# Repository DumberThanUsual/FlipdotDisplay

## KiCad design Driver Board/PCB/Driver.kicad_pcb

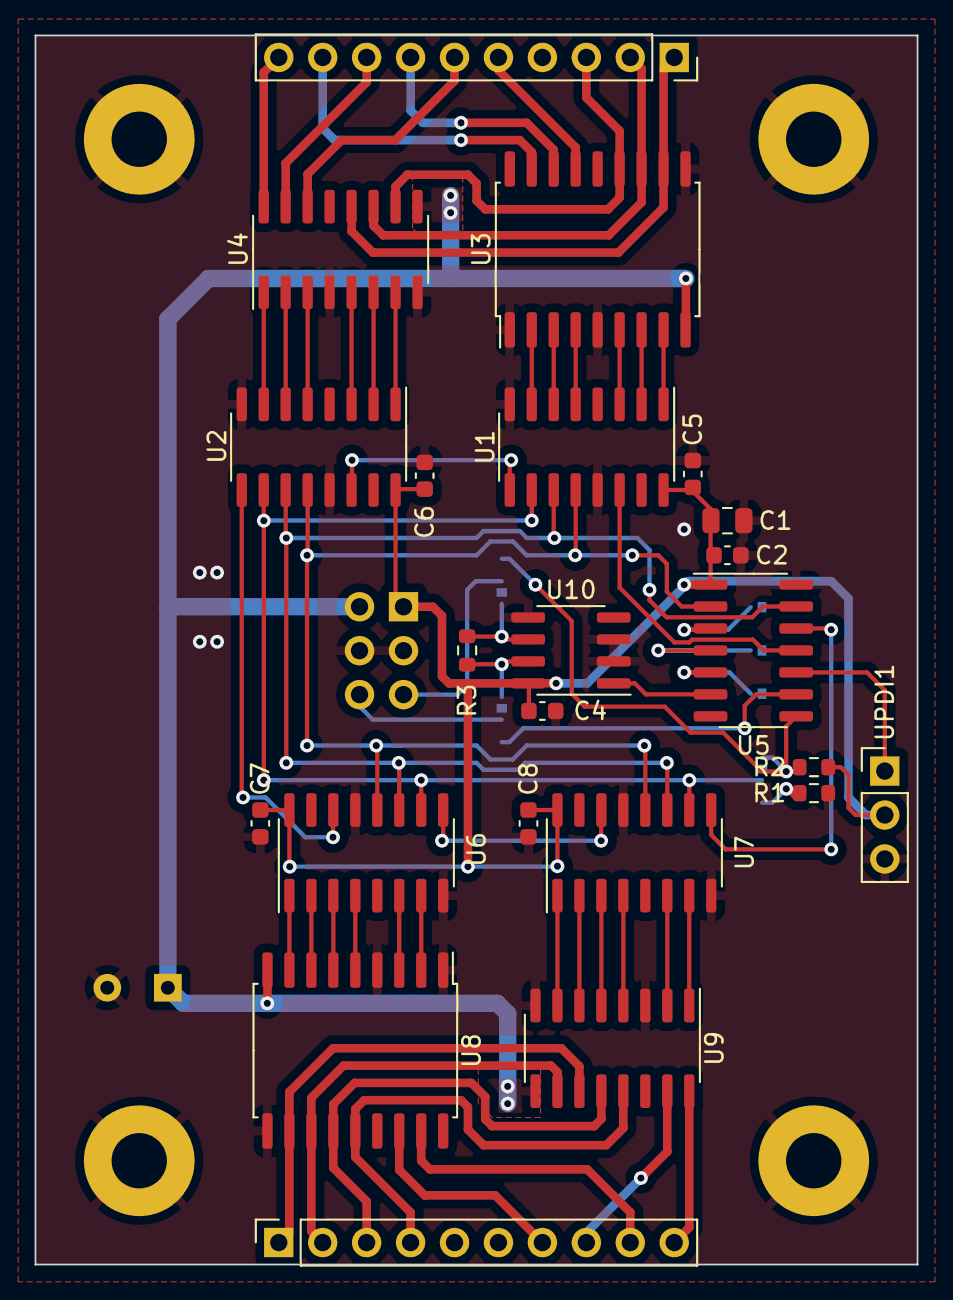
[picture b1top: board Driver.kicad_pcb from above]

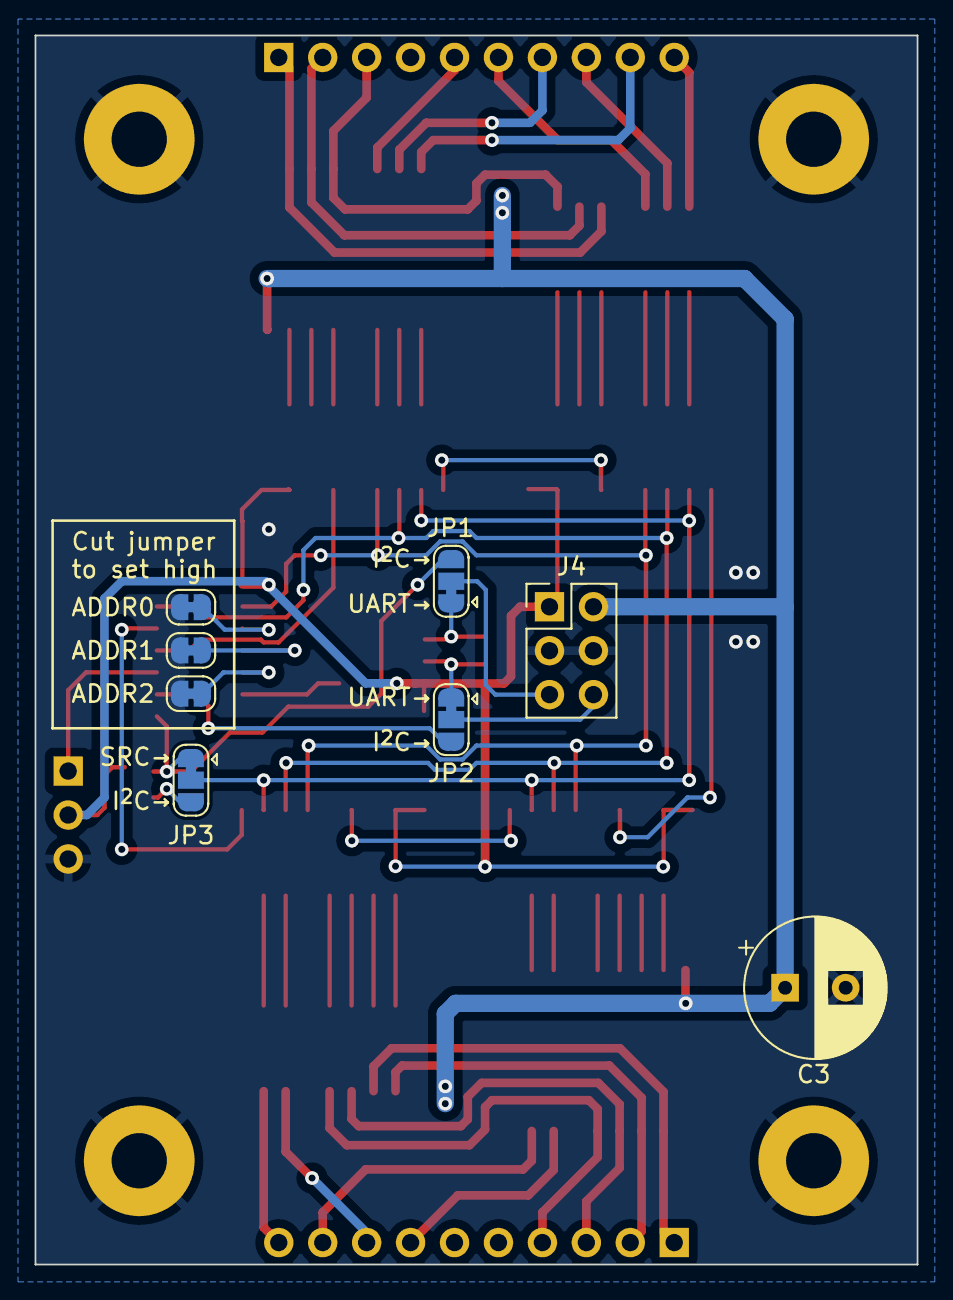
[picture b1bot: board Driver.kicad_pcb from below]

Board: 2 copper layers, 51.0 x 71.0 mm, 35 parts (8 on the bottom side), 64 nets.

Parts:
ADDR0: ADDR0; SolderJumper-2_P1.3mm_Bridged_RoundedPad1.0x1.5mm
ADDR1: ADDR1; SolderJumper-2_P1.3mm_Bridged_RoundedPad1.0x1.5mm
ADDR2: ADDR2; SolderJumper-2_P1.3mm_Bridged_RoundedPad1.0x1.5mm
C1: 22u; C_0805_2012Metric
C2, C4, C5, C6, C7, C8: 100n; C_0603_1608Metric
C3: 470u; CP_Radial_D8.0mm_P3.50mm
H1, H2, H3, H4: MountingHole; MountingHole_3.2mm_M3_Pad
J2, J3: Conn_01x10_Pin; PinSocket_1x10_P2.54mm_Vertical
J4: BHR-06-VUA; PinHeader_2x03_P2.54mm_Vertical
JP1, JP2, JP3: SolderJumper_3_Bridged12; SolderJumper-3_P1.3mm_Bridged12_RoundedPad1.0x1.5mm
R1, R2: 100k; R_0603_1608Metric
R3: R_{term}; R_0603_1608Metric
U1, U2, U6, U7: 74HC595; SOIC-16_3.9x9.9mm_P1.27mm
U3, U8: TBD62783A; SOIC-18W_7.5x11.6mm_P1.27mm
U4, U9: ULN2003A; SOIC-16_3.9x9.9mm_P1.27mm
U5: ATtiny424-SS; SOIC-14_3.9x8.7mm_P1.27mm
U10: THVD1420D; SOIC-8_3.9x4.9mm_P1.27mm
UPDI1: Conn_01x03_Pin; PinHeader_1x03_P2.54mm_Vertical

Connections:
/C1H: J3.9, U3.17 (O2)
/C1L: J3.10, U4.16 (O1)
/C2H: J3.7, U3.16 (O3)
/C2L: J3.8, U4.15 (O2)
/C3H: J3.5, U3.15 (O4)
/C3L: J3.6, U4.14 (O3)
/C4H: J2.7, U8.16 (O3)
/C4L: J2.8, U9.15 (O2)
/C5H: J2.9, U8.17 (O2)
/C5L: J2.10, U9.16 (O1)
/D1: U1.1 (QB), U3.8 (I8)
/D2: U1.2 (QC), U3.7 (I7)
/D3: U1.3 (QD), U3.6 (I6)
/D5: U1.5 (QF), U3.4 (I4)
/D6: U1.6 (QG), U3.3 (I3)
/D7: U1.7 (QH), U3.2 (I2)
/D9: U2.1 (QB), U4.7 (I7)
/D10: U2.2 (QC), U4.6 (I6)
/D11: U2.3 (QD), U4.5 (I5)
/D13: U2.5 (QF), U4.3 (I3)
/D14: U2.6 (QG), U4.2 (I2)
/D15: U2.7 (QH), U4.1 (I1)
/D17: U6.1 (QB), U8.8 (I8)
/D18: U6.2 (QC), U8.7 (I7)
/D19: U6.3 (QD), U8.6 (I6)
/D20: U6.4 (QE), U8.5 (I5)
/D22: U6.6 (QG), U8.3 (I3)
/D23: U6.7 (QH), U8.2 (I2)
/D25: U7.1 (QB), U9.7 (I7)
/D26: U7.2 (QC), U9.6 (I6)
/D27: U7.3 (QD), U9.5 (I5)
/D28: U7.4 (QE), U9.4 (I4)
/D30: U7.6 (QG), U9.2 (I2)
/D31: U7.7 (QH), U9.1 (I1)
/I^{2}C_SCL: JP2.3 (B), U5.9 (PB0)
/I^{2}C_SDA: JP1.3 (B), JP3.1 (A), R2.2, U5.8 (PB1)
/RCLK: U1.12 (RCLK), U2.12 (RCLK), U5.2 (PA4), U6.12 (RCLK), U7.12 (RCLK)
/RS485_A: JP1.1 (A), R3.1, U10.6 (A)
/RS485_B: JP2.1 (A), R3.2, U10.7 (B)
/SA: J2.1, U8.11 (O8), U9.11 (O6)
/SB: J2.2, U8.12 (O7), U9.10 (O7)
/SC: J2.3, U8.13 (O6), U9.12 (O5)
/SD: J2.4, U8.14 (O5), U9.13 (O4)
/SE: J3.3, U3.13 (O6), U4.10 (O7)
/SER': U2.9 (QH'), U6.14 (SER)
/SEROUT: U5.12 (PA2), U7.9 (QH')
/SF: J3.2, U3.12 (O7), U4.11 (O6)
/SG: J3.1, U3.11 (O8), U4.12 (O5)
/SRCLK: U1.11 (SRCLK), U2.11 (SRCLK), U5.13 (PA3), U6.11 (SRCLK), U7.11 (SRCLK)
/SRIN: U1.14 (SER), U5.11 (PA1)
/UART_RXD: U5.6 (PB3), U10.1 (RO)
/~RST/UPDI: U5.10 (~RESET/PA0), UPDI1.1
/~SRCLR: JP3.2 (C), U1.10 (~SRCLR), U2.10 (~SRCLR), U6.10 (~SRCLR), U7.10 (~SRCLR)
GND: ADDR0.2 (B), ADDR1.2 (B), ADDR2.2 (B), C1.2, C2.2, C3.2, C4.2, C5.2, C6.2, C7.2, C8.2, H1.1, H2.1, H3.1, H4.1, J4.3, J4.4, R1.1, U1.8 (GND), U1.13 (~OE), U2.8 (GND), U2.13 (~OE), U3.1 (I1), U3.5 (I5), U3.10 (GND), U4.4 (I4), U4.8 (GND), U5.14 (GND), U6.8 (GND), U6.13 (~OE), U7.8 (GND), U7.13 (~OE), U8.1 (I1), U8.4 (I4), U8.10 (GND), U9.3 (I3), U9.8 (GND), U10.2 (~RE), U10.3 (DE), U10.5 (GND), UPDI1.3
unnamed: ADDR0.1 (A), U5.3 (PA5)
unnamed: ADDR1.1 (A), U5.4 (PA6)
unnamed: ADDR2.1 (A), U5.5 (PA7)
unnamed: J4.5, JP1.2 (C)
unnamed: J4.6, JP2.2 (C)
unnamed: JP3.3 (B), R1.2
unnamed: U1.9 (QH'), U2.14 (SER)
unnamed: U6.9 (QH'), U7.14 (SER)
VCC: C1.1, C2.1, C4.1, C5.1, C6.1, C7.1, C8.1, J4.1, R2.1, U1.16 (VCC), U2.16 (VCC), U5.1 (VCC), U6.16 (VCC), U7.16 (VCC), U10.8 (VCC), UPDI1.2
Vdrive: C3.1, J4.2, U3.9 (VCC), U4.9 (COM), U8.9 (VCC), U9.9 (COM)

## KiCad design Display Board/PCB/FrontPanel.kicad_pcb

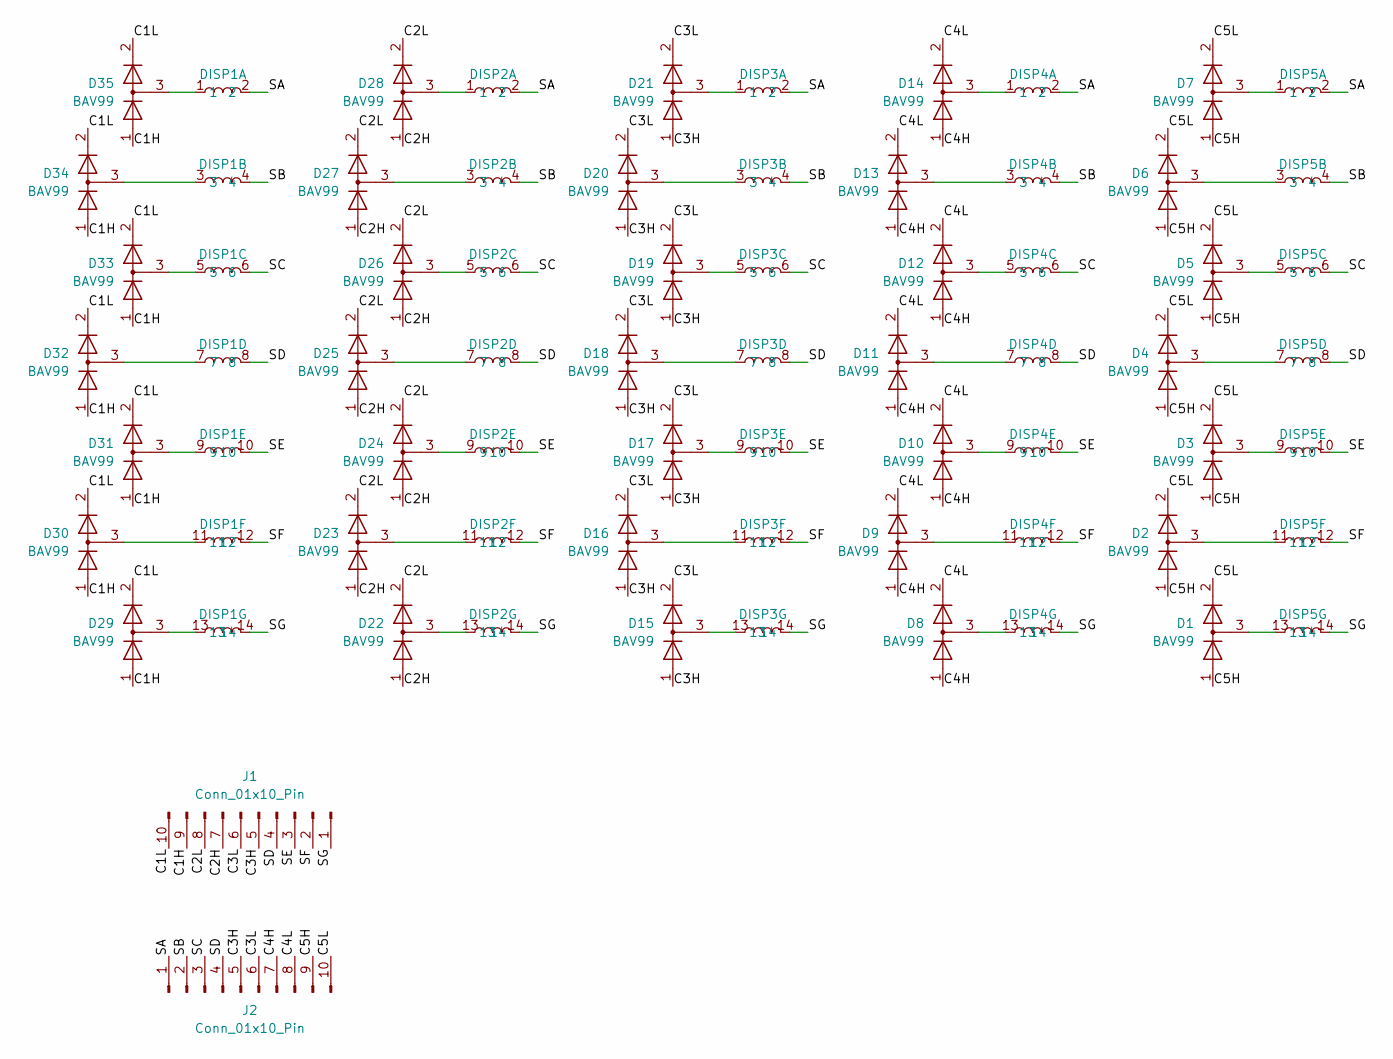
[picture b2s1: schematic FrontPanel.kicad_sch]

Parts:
D1, D2, D3, D4, D5, D6, D7, D8, D9, D10, D11, D12, D13, D14, D15, D16, D17, D18, D19, D20, D21, D22, D23, D24, D25, D26, D27, D28, D29, D30, D31, D32, D33, D34, D35: BAV99; SOT-23
DISP1, DISP2, DISP3, DISP4, DISP5: 1x7
J1, J2: Conn_01x10_Pin; PinHeader_1x10_P2.54mm_Vertical

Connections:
/C1H: D29.1 (K), D30.1 (K), D31.1 (K), D32.1 (K), D33.1 (K), D34.1 (K), D35.1 (K), J1.9
/C1L: D29.2 (A), D30.2 (A), D31.2 (A), D32.2 (A), D33.2 (A), D34.2 (A), D35.2 (A), J1.10
/C2H: D22.1 (K), D23.1 (K), D24.1 (K), D25.1 (K), D26.1 (K), D27.1 (K), D28.1 (K), J1.7
/C2L: D22.2 (A), D23.2 (A), D24.2 (A), D25.2 (A), D26.2 (A), D27.2 (A), D28.2 (A), J1.8
/C3H: D15.1 (K), D16.1 (K), D17.1 (K), D18.1 (K), D19.1 (K), D20.1 (K), D21.1 (K), J1.5, J2.5
/C3L: D15.2 (A), D16.2 (A), D17.2 (A), D18.2 (A), D19.2 (A), D20.2 (A), D21.2 (A), J1.6, J2.6
/C4H: D8.1 (K), D9.1 (K), D10.1 (K), D11.1 (K), D12.1 (K), D13.1 (K), D14.1 (K), J2.7
/C4L: D8.2 (A), D9.2 (A), D10.2 (A), D11.2 (A), D12.2 (A), D13.2 (A), D14.2 (A), J2.8
/C5H: D1.1 (K), D2.1 (K), D3.1 (K), D4.1 (K), D5.1 (K), D6.1 (K), D7.1 (K), J2.9
/C5L: D1.2 (A), D2.2 (A), D3.2 (A), D4.2 (A), D5.2 (A), D6.2 (A), D7.2 (A), J2.10
/SA: DISP1.2, DISP2.2, DISP3.2, DISP4.2, DISP5.2, J2.1
/SB: DISP1.4, DISP2.4, DISP3.4, DISP4.4, DISP5.4, J2.2
/SC: DISP1.6, DISP2.6, DISP3.6, DISP4.6, DISP5.6, J2.3
/SD: DISP1.8, DISP2.8, DISP3.8, DISP4.8, DISP5.8, J1.4, J2.4
/SE: DISP1.10, DISP2.10, DISP3.10, DISP4.10, DISP5.10, J1.3
/SF: DISP1.12, DISP2.12, DISP3.12, DISP4.12, DISP5.12, J1.2
/SG: DISP1.14, DISP2.14, DISP3.14, DISP4.14, DISP5.14, J1.1
unnamed: D1.3 (K), DISP5.13
unnamed: D2.3 (K), DISP5.11
unnamed: D3.3 (K), DISP5.9
unnamed: D4.3 (K), DISP5.7
unnamed: D5.3 (K), DISP5.5
unnamed: D6.3 (K), DISP5.3
unnamed: D7.3 (K), DISP5.1
unnamed: D8.3 (K), DISP4.13
unnamed: D9.3 (K), DISP4.11
unnamed: D10.3 (K), DISP4.9
unnamed: D11.3 (K), DISP4.7
unnamed: D12.3 (K), DISP4.5
unnamed: D13.3 (K), DISP4.3
unnamed: D14.3 (K), DISP4.1
unnamed: D15.3 (K), DISP3.13
unnamed: D16.3 (K), DISP3.11
unnamed: D17.3 (K), DISP3.9
unnamed: D18.3 (K), DISP3.7
unnamed: D19.3 (K), DISP3.5
unnamed: D20.3 (K), DISP3.3
unnamed: D21.3 (K), DISP3.1
unnamed: D22.3 (K), DISP2.13
unnamed: D23.3 (K), DISP2.11
unnamed: D24.3 (K), DISP2.9
unnamed: D25.3 (K), DISP2.7
unnamed: D26.3 (K), DISP2.5
unnamed: D27.3 (K), DISP2.3
unnamed: D28.3 (K), DISP2.1
unnamed: D29.3 (K), DISP1.13
unnamed: D30.3 (K), DISP1.11
unnamed: D31.3 (K), DISP1.9
unnamed: D32.3 (K), DISP1.7
unnamed: D33.3 (K), DISP1.5
unnamed: D34.3 (K), DISP1.3
unnamed: D35.3 (K), DISP1.1

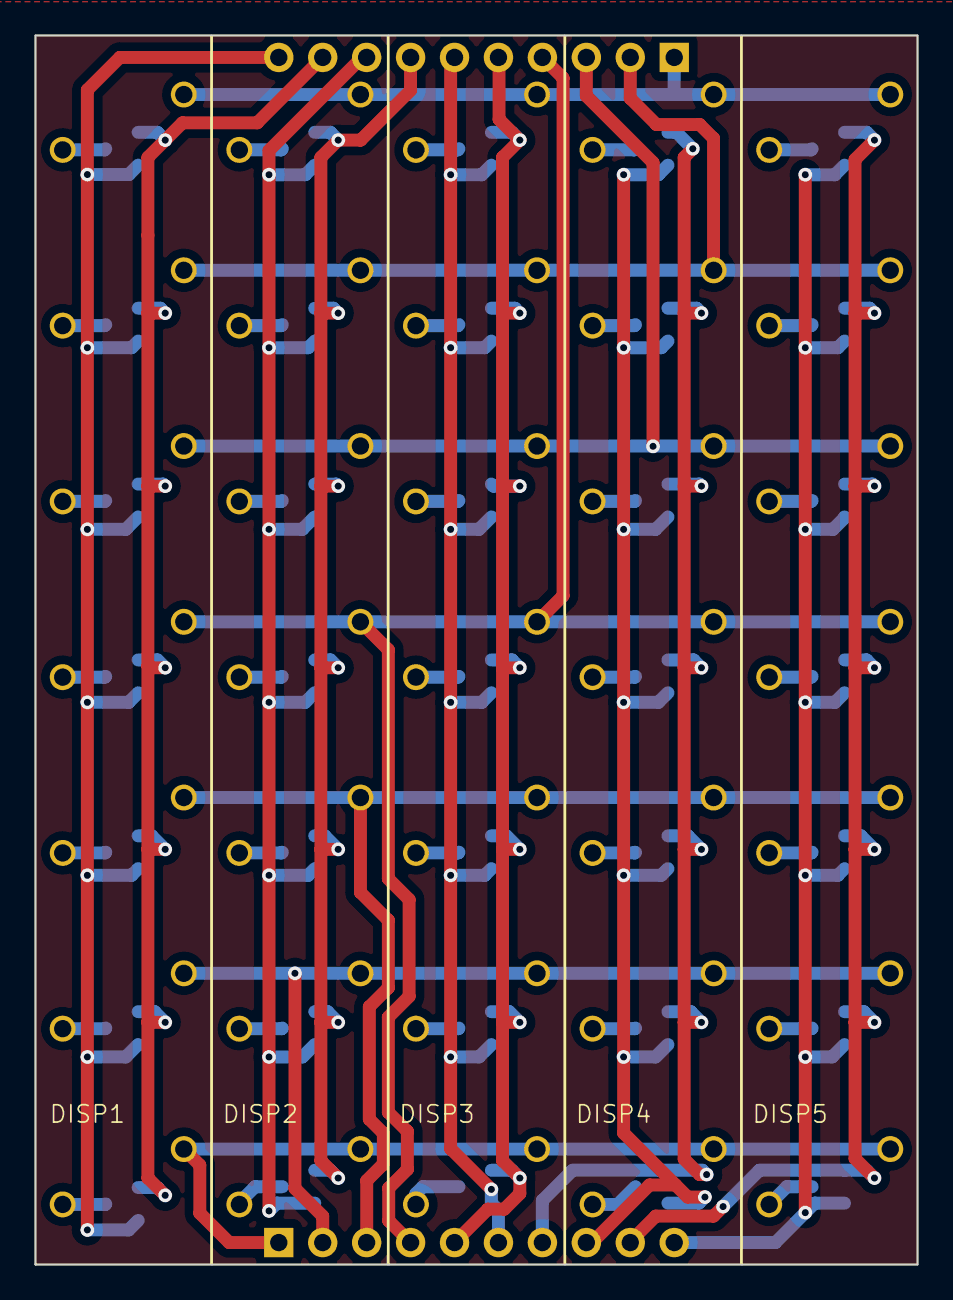
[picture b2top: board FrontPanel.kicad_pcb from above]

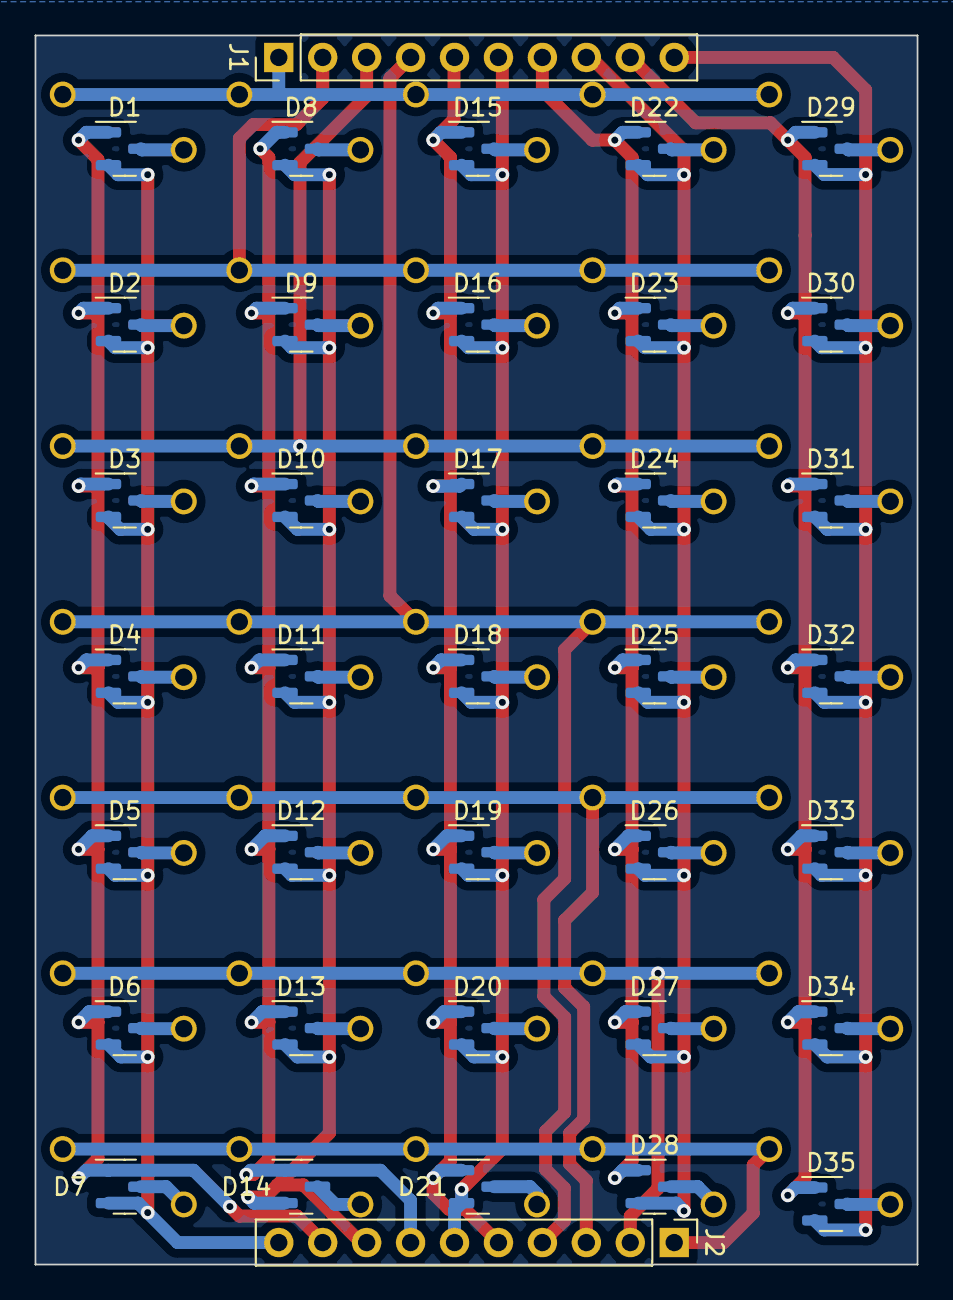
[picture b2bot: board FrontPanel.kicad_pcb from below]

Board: 2 copper layers, 51.0 x 71.0 mm, 42 parts (37 on the bottom side), 52 nets.

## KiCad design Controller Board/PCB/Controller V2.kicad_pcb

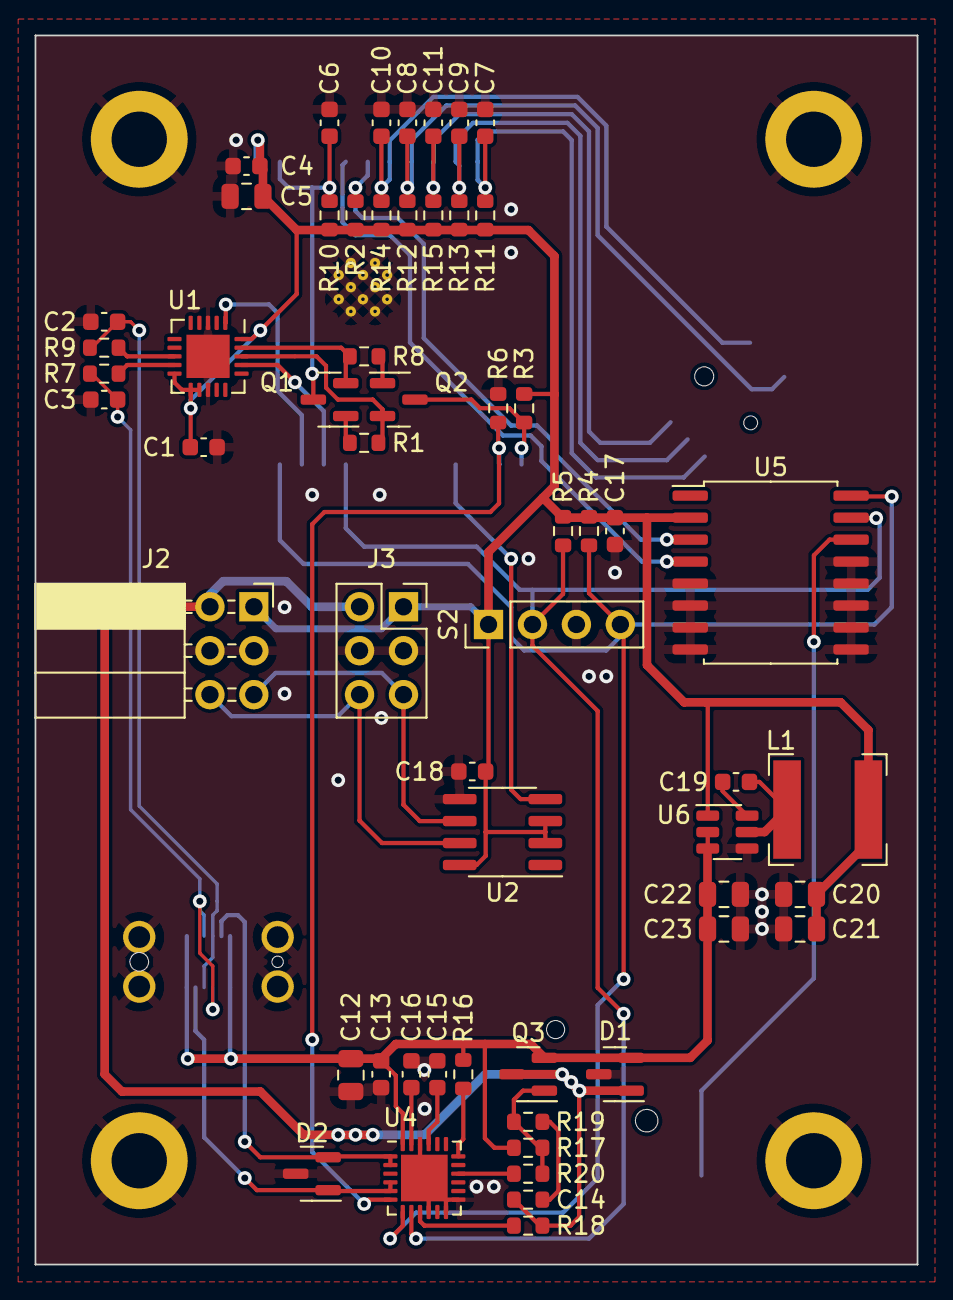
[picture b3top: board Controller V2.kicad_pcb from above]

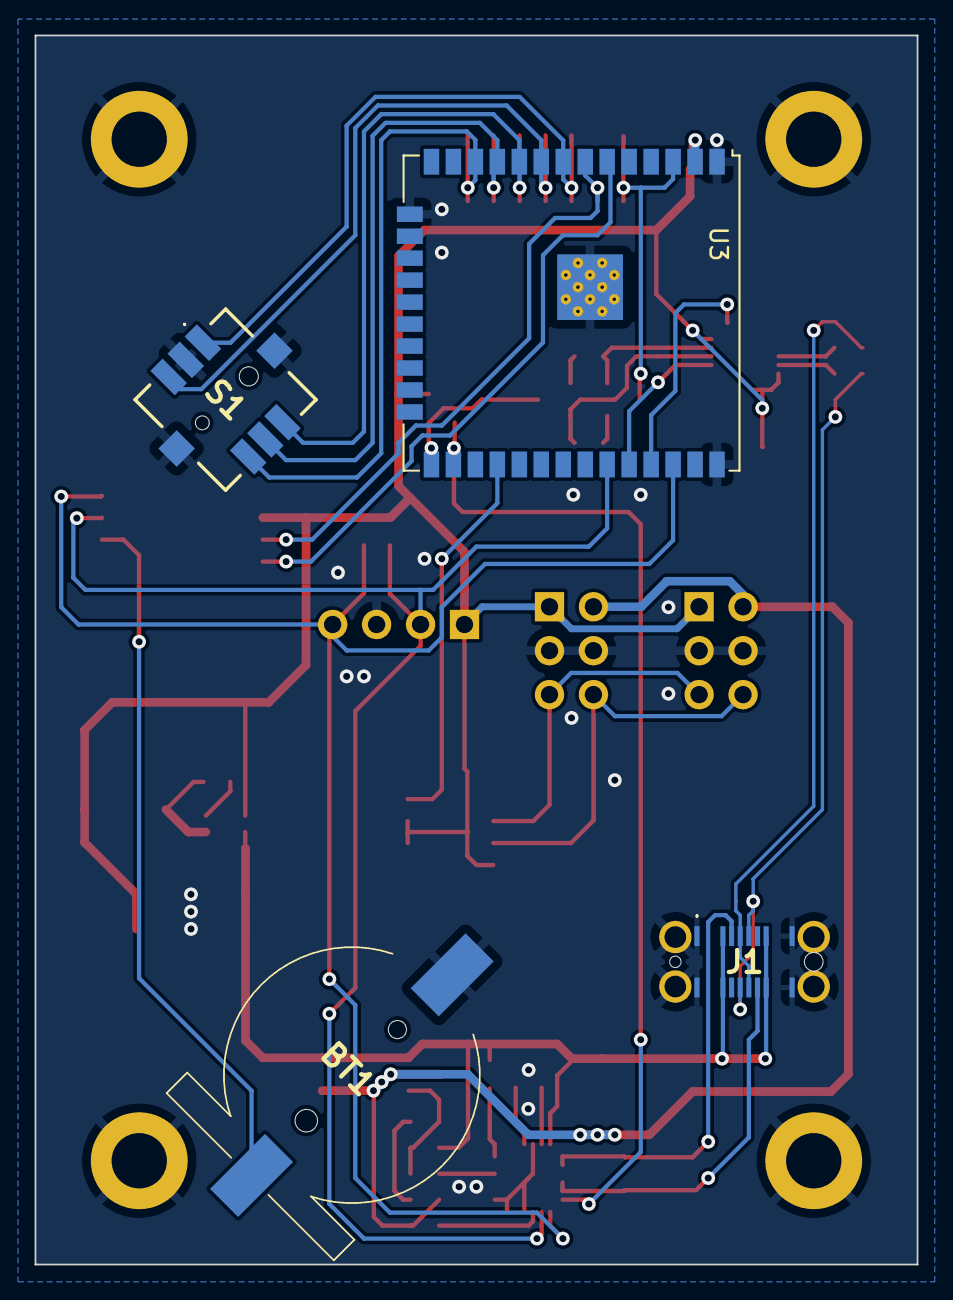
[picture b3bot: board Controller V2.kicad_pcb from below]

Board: 2 copper layers, 51.0 x 71.0 mm, 65 parts (4 on the bottom side), 41 nets.

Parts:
BT1: CR2032; S8411-45
C1, C4, C7, C8, C9, C10, C11, C17, C18, C19: 100n; C_0603_1608Metric
C2, C3: 47p; C_0603_1608Metric
C5, C20, C21: 22u; C_0805_2012Metric
C6, C13, C15, C16: 1u; C_0603_1608Metric
C12, C22, C23: 4.7u; C_0805_2012Metric
C14: 100n; R_0603_1608Metric
D1, D2: MMBZ27; SOT-23
H1, H2, H3, H4: MountingHole_Pad; MountingHole_3.2mm_M3_DIN965_Pad
J1: USB4145-03-0230; USB4145030230C
J2: BHR-06; PinSocket_2x03_P2.54mm_Horizontal
J3: SFH11; PinSocket_2x03_P2.54mm_Vertical
L1: 3.9u; L_Bourns-SRN6028
Q1, Q2: BC817; SOT-23
Q3: DMP3099; SOT-23
R1, R2, R3, R6, R8, R10, R11, R12, R13, R14, R15: 10k; R_0603_1608Metric
R4, R5, R16, R18: 1k; R_0603_1608Metric
R7, R9: 27; R_0603_1608Metric
R17: 100k; R_0603_1608Metric
R19: 100; R_0603_1608Metric
R20: 22k; R_0603_1608Metric
S1: TS12-74-70-BK-250; TS127460BK250SMTTR
S2: AHT20; PinHeader_1x04_P2.54mm_Vertical
U1: FT231XQ; QFN-20-1EP_4x4mm_P0.5mm_EP2.5x2.5mm
U2: THVD1420D; SOIC-8_3.9x4.9mm_P1.27mm
U3: ESP32-WROOM-32UE
U4: STUSB4500QTR; QFN-24-1EP_4x4mm_P0.5mm_EP2.7x2.7mm
U5: DS3231M; SOIC-16W_7.5x10.3mm_P1.27mm
U6: AP63203WU; TSOT-23-6

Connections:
+3V3: C1.1, C4.1, C5.1, C17.1, C18.1, C20.1, C21.1, J2.1, J3.1, L1.2, R2.1, R3.1, R4.1, R5.1, R10.1, R11.1, R12.1, R13.1, R14.1, R15.1, S2.1, U1.10 (3V3OUT), U1.11 (~RESET), U1.12 (VCC), U1.20 (VCCIO), U2.2 (~RE), U2.3 (DE), U2.8 (VCC), U3.2 (VDD), U5.2 (VCC), U6.1 (FB)
/CC1: D2.2 (K), J1.A5 (CC1), U4.1 (CC1DB), U4.2 (CC1)
/CC2: D2.1 (K), J1.B5 (CC2), U4.4 (CC2), U4.5 (CC2DB)
/D+: C2.1, J1.A6 (DP1), J1.B6 (DP2), R9.1
/D-: C3.1, J1.A7 (DN1), J1.B7 (DN2), R7.1
/DISPLAY_RX: U2.4 (DI), U3.28 (IO17)
/DTR: Q2.2 (E), R1.1, U1.18 (~DTR)
/EN: C6.1, Q1.3 (C), R10.2, U3.3 (EN)
/FT_RX: U1.1 (RXD), U3.35 (TXD0/IO1)
/FT_TX: U1.17 (TXD), U3.34 (RXD0/IO3)
/IO0: Q2.3 (C), R3.2, U3.25 (IO0)
/RS485_A: J2.5, J3.5, U2.6 (A)
/RS485_B: J2.6, J3.6, U2.7 (B)
/RTC_INT: R2.2, U3.7 (IO35), U5.3 (~INT/SQW)
/RTC_RESET: U3.6 (IO34), U5.4 (~RST)
/RTC_VBAT: BT1.1 (+), U5.14 (VBAT)
/RTS: Q1.2 (E), R8.1, U1.19 (~RTS)
/SCL: R4.2, S2.4, U3.36 (IO22), U4.7 (SCL), U5.16 (SCL)
/SDA: R5.2, S2.2, U3.33 (IO21), U4.8 (SDA), U5.15 (SDA)
/STUSB_RESET: R6.1, U3.26 (IO4), U4.6 (RESET)
/SW_BACK: C8.1, R12.2, S1.3 (F4), U3.9 (IO33)
/SW_CENTER: C9.1, R13.2, S1.5 (NO), U3.11 (IO26)
/SW_DN: C7.1, R11.2, S1.4 (F5), U3.12 (IO27)
/SW_ENTER: C11.1, R15.2, S1.6 (F3), U3.10 (IO25)
/SW_UP: C10.1, R14.2, S1.1 (F2), U3.8 (IO32)
/VBUS_DISCH: R16.2, U4.18 (VBUS_VS_DISCH)
/VDRIVE_DISCH: R18.2, U4.9 (DISCH)
GND: BT1.2 (-), C1.2, C2.2, C3.2, C4.2, C5.2, C6.2, C7.2, C8.2, C9.2, C10.2, C11.2, C12.2, C13.2, C15.1, C16.2, C17.2, C18.2, C20.2, C21.2, C22.2, C23.2, D1.3 (A), D2.3 (A), H1.1, H2.1, H3.1, H4.1, J1.A1 (GND_1), J1.A12 (GND_2), J1.B1 (GND_3), J1.B12 (GND_4), J1.MH1 (MH5), J1.MH2 (MH6), J1.MH3, J1.MH4, J2.3, J2.4, J3.3, J3.4, R6.2, S1.2 (COM), S1.MP1, S1.MP2, S2.3, U1.3 (GND), U1.13 (GND), U1.21 (GND), U2.5 (GND), U3.1 (GND), U3.15 (GND), U3.38 (GND), U3.39 (GND), U4.10 (GND), U4.12 (ADDR0), U4.13 (ADDR1), U4.22 (VSYS), U4.25 (GND), U5.5 (GND), U5.6 (GND), U5.7 (GND), U5.8 (GND), U5.9 (GND), U5.10 (GND), U5.11 (GND), U5.12 (GND), U5.13 (GND), U6.4 (GND)
unnamed: C14.2, R19.1
unnamed: Q1.1 (B), R1.2
unnamed: Q2.1 (B), R8.2
unnamed: Q3.1 (G), R17.1, R19.2, R20.2
unnamed: R7.2, U1.9 (USBDM)
unnamed: R9.2, U1.8 (USBDP)
unnamed: R20.1, U4.16 (VBUS_EN_SNK)
unnamed: C15.2, U4.21 (VREG_1V2)
unnamed: C16.1, U4.23 (VREG_2V7)
unnamed: C19.1, U6.6 (BST)
unnamed: C19.2, L1.1, U6.5 (SW)
VBUS: C12.1, C13.1, C22.1, C23.1, D1.2 (K), J1.A4 (VBUS_1), J1.A9 (VBUS_2), J1.B4 (VBUS_3), J1.B9 (VBUS_4), Q3.2 (S), R16.1, R17.2, U4.24 (VDD), U6.2 (EN), U6.3 (IN)
Vdrive: C14.1, D1.1 (K), J2.2, J3.2, Q3.3 (D), R18.1
